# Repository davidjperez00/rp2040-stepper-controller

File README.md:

# rp2040-stepper-controller
This project utilizes the RP2040 microcontroller and A4988 motor drivers on a custom PCB to control NEMA-17 stepper motors. This PCB is equipped with four A4988 providing the ability to drive multiple motors from a single microntroller. Headers pins provide the ability of micro-stepping for each motor. The micro-USB allows for easy flashing from a host machine. The 32MB of external flash memory provide the ability to flash large programs.

## Demo (Click Thumbnail to see Youtube video)

## PCB Snapshots

## Schematic Snapshots

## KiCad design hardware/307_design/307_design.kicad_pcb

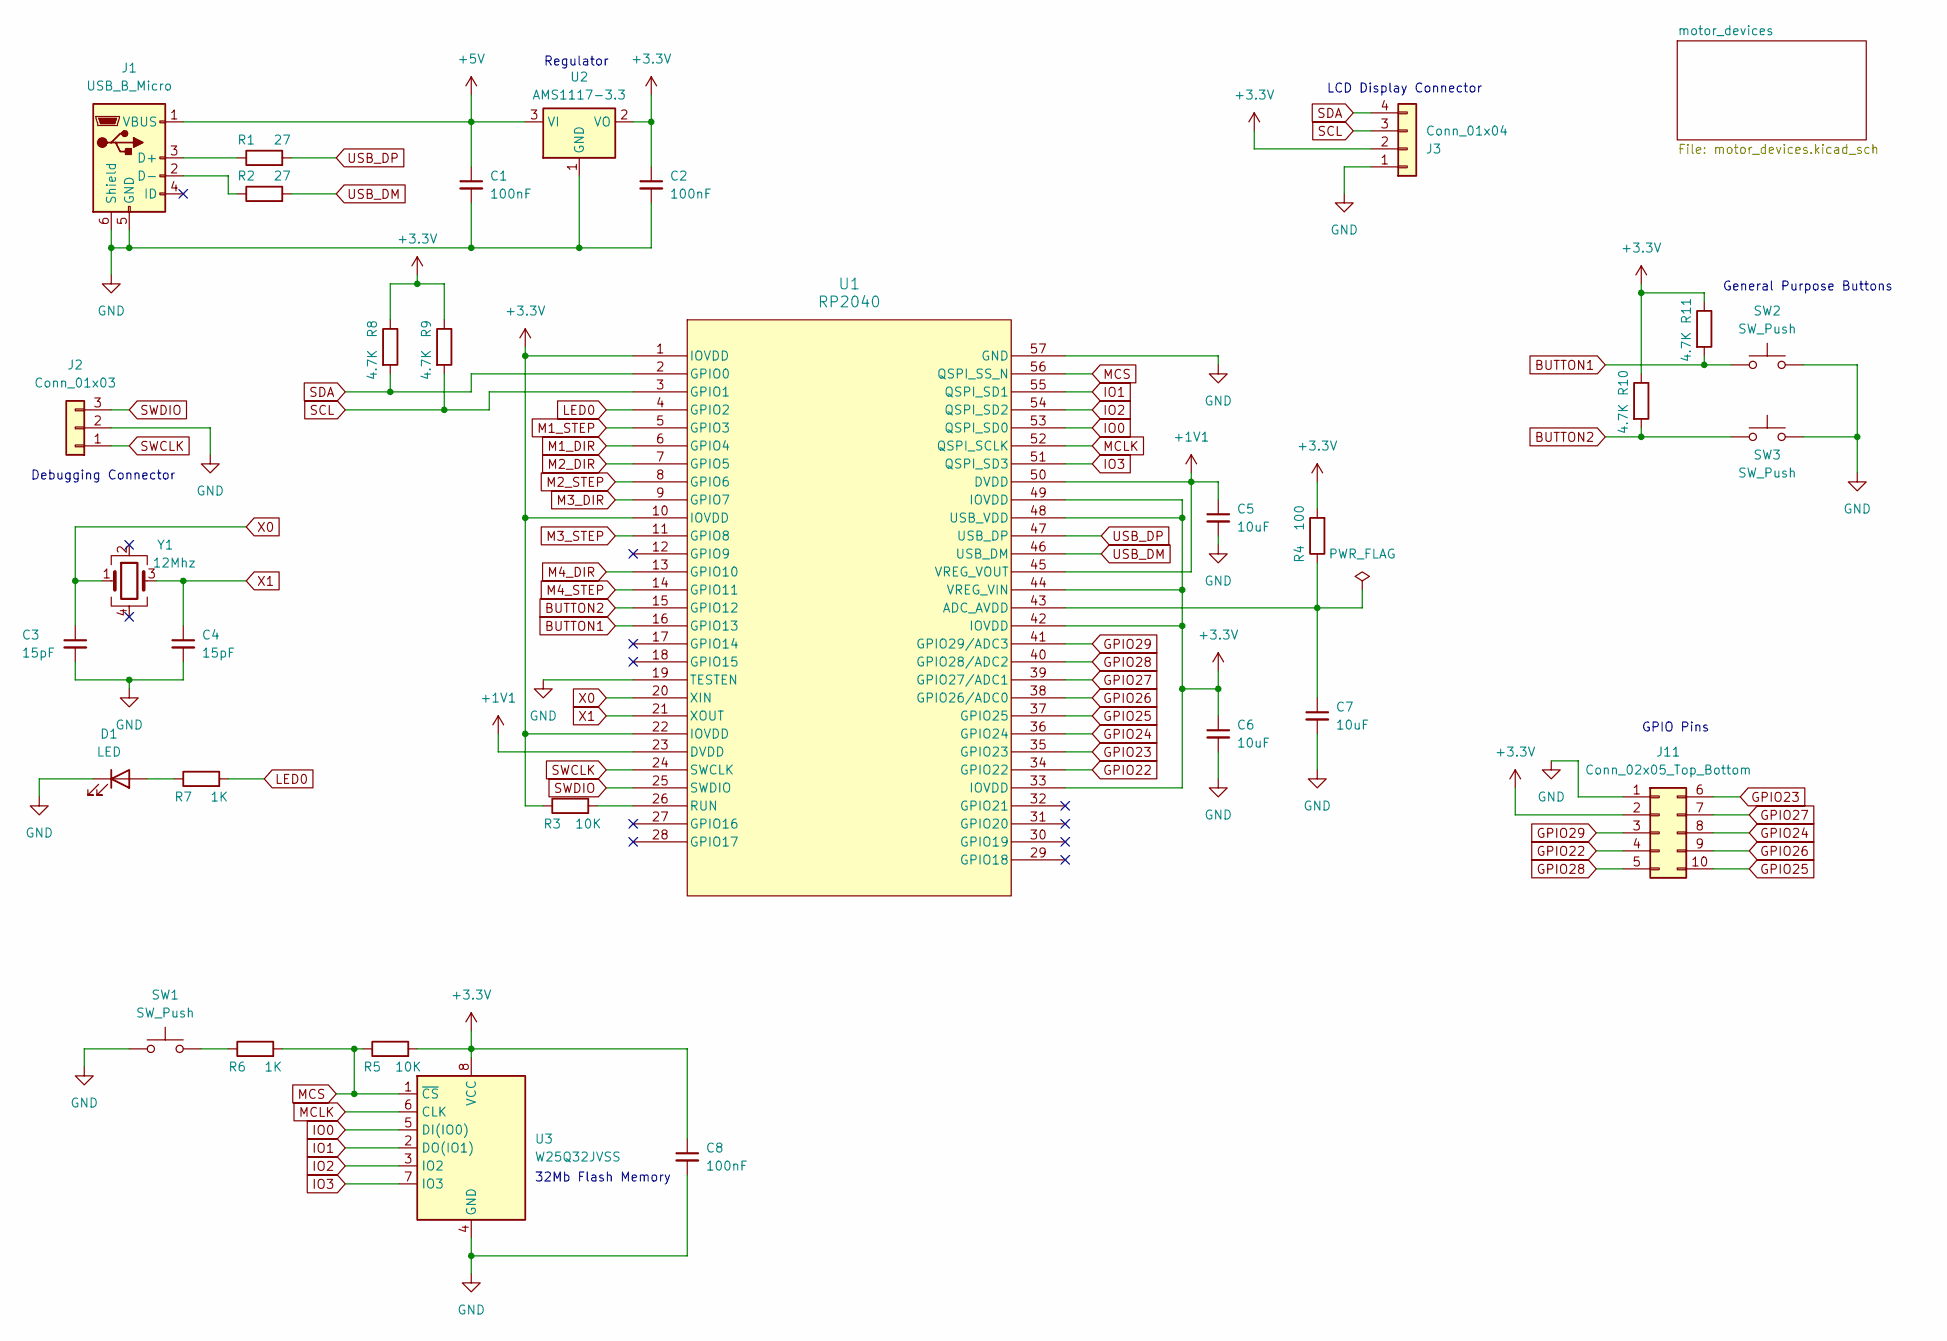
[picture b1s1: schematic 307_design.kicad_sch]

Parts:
C1, C2, C8: 100nF; C_0805_2012Metric
C3, C4: 15pF; C_0805_2012Metric
C5, C6, C7: 10uF; C_0805_2012Metric
D1: LED; LED_0805_2012Metric
J1: USB_B_Micro; USB_Micro-B_Molex_47346-0001
J2: Conn_01x03; PinHeader_1x03_P2.54mm_Vertical
J3: Conn_01x04; PinHeader_1x04_P2.54mm_Vertical
J11: Conn_02x05_Top_Bottom; PinHeader_2x05_P2.54mm_Vertical
R1, R2: 27; R_0805_2012Metric
R3, R5: 10K; R_0805_2012Metric
R4: 100; R_0805_2012Metric
R6, R7: 1K; R_0805_2012Metric
R8, R9, R10, R11: 4.7K; R_0805_2012Metric
SW1, SW2, SW3: SW_Push; SW_SPST_CK_RS282G05A3
U1: RP2040; IC57_RP2040
U2: AMS1117-3.3; SOT-223-3_TabPin2
U3: W25Q32JVSS; SOIC-8_5.23x5.23mm_P1.27mm
Y1: 12Mhz; Crystal_SMD_SeikoEpson_FA238-4Pin_3.2x2.5mm

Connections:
+1V1: C5.1, U1.23 (DVDD), U1.45 (VREG_VOUT), U1.50 (DVDD)
+3.3V: C2.1, C6.1, C8.1, J3.2, J11.2, R3.1, R4.2, R5.2, R8.1, R9.1, R10.1, R11.1, U1.1 (IOVDD), U1.10 (IOVDD), U1.22 (IOVDD), U1.33 (IOVDD), U1.42 (IOVDD), U1.44 (VREG_VIN), U1.48 (USB_VDD), U1.49 (IOVDD), U2.2 (VO), U3.8 (VCC); also elsewhere on the board
+5V: C1.1, J1.1 (VBUS), U2.3 (VI)
BUTTON1: R11.2, SW2.1, U1.16 (GPIO13)
BUTTON2: R10.2, SW3.1, U1.15 (GPIO12)
GPIO22: J11.4, U1.34 (GPIO22)
GPIO23: J11.6, U1.35 (GPIO23)
GPIO24: J11.8, U1.36 (GPIO24)
GPIO25: J11.10, U1.37 (GPIO25)
GPIO26: J11.9, U1.38 (GPIO26/ADC0)
GPIO27: J11.7, U1.39 (GPIO27/ADC1)
GPIO28: J11.5, U1.40 (GPIO28/ADC2)
GPIO29: J11.3, U1.41 (GPIO29/ADC3)
IO0: U1.53 (QSPI_SD0), U3.5 (DI(IO0))
IO1: U1.55 (QSPI_SD1), U3.2 (DO(IO1))
IO2: U1.54 (QSPI_SD2), U3.3 (IO2)
IO3: U1.51 (QSPI_SD3), U3.7 (IO3)
LED0: R7.2, U1.4 (GPIO2)
M1_DIR: U1.6 (GPIO4); also elsewhere on the board
M1_STEP: U1.5 (GPIO3); also elsewhere on the board
M2_DIR: U1.7 (GPIO5); also elsewhere on the board
M2_STEP: U1.8 (GPIO6); also elsewhere on the board
M3_DIR: U1.9 (GPIO7); also elsewhere on the board
M3_STEP: U1.11 (GPIO8); also elsewhere on the board
M4_DIR: U1.13 (GPIO10); also elsewhere on the board
M4_STEP: U1.14 (GPIO11); also elsewhere on the board
MCLK: U1.52 (QSPI_SCLK), U3.6 (CLK)
MCS: R5.1, R6.2, U1.56 (QSPI_SS_N), U3.1 (~CS)
unnamed: D1.2 (A), R7.1
unnamed: J1.3 (D+), R1.1
unnamed: J1.2 (D-), R2.1
unnamed: R6.1, SW1.2
unnamed: C7.1, R4.1, U1.43 (ADC_AVDD)
unnamed: R3.2, U1.26 (RUN)
SCL: J3.3, R9.2, U1.3 (GPIO1)
SDA: J3.4, R8.2, U1.2 (GPIO0)
SWCLK: J2.1, U1.24 (SWCLK)
SWDIO: J2.3, U1.25 (SWDIO)
USB_DM: R2.2, U1.46 (USB_DM)
USB_DP: R1.2, U1.47 (USB_DP)
X0: C3.1, U1.20 (XIN), Y1.1
X1: C4.1, U1.21 (XOUT), Y1.3

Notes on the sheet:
General Purpose Buttons
Debugging Connector
GPIO Pins
LCD Display Connector
Regulator
32Mb Flash Memory

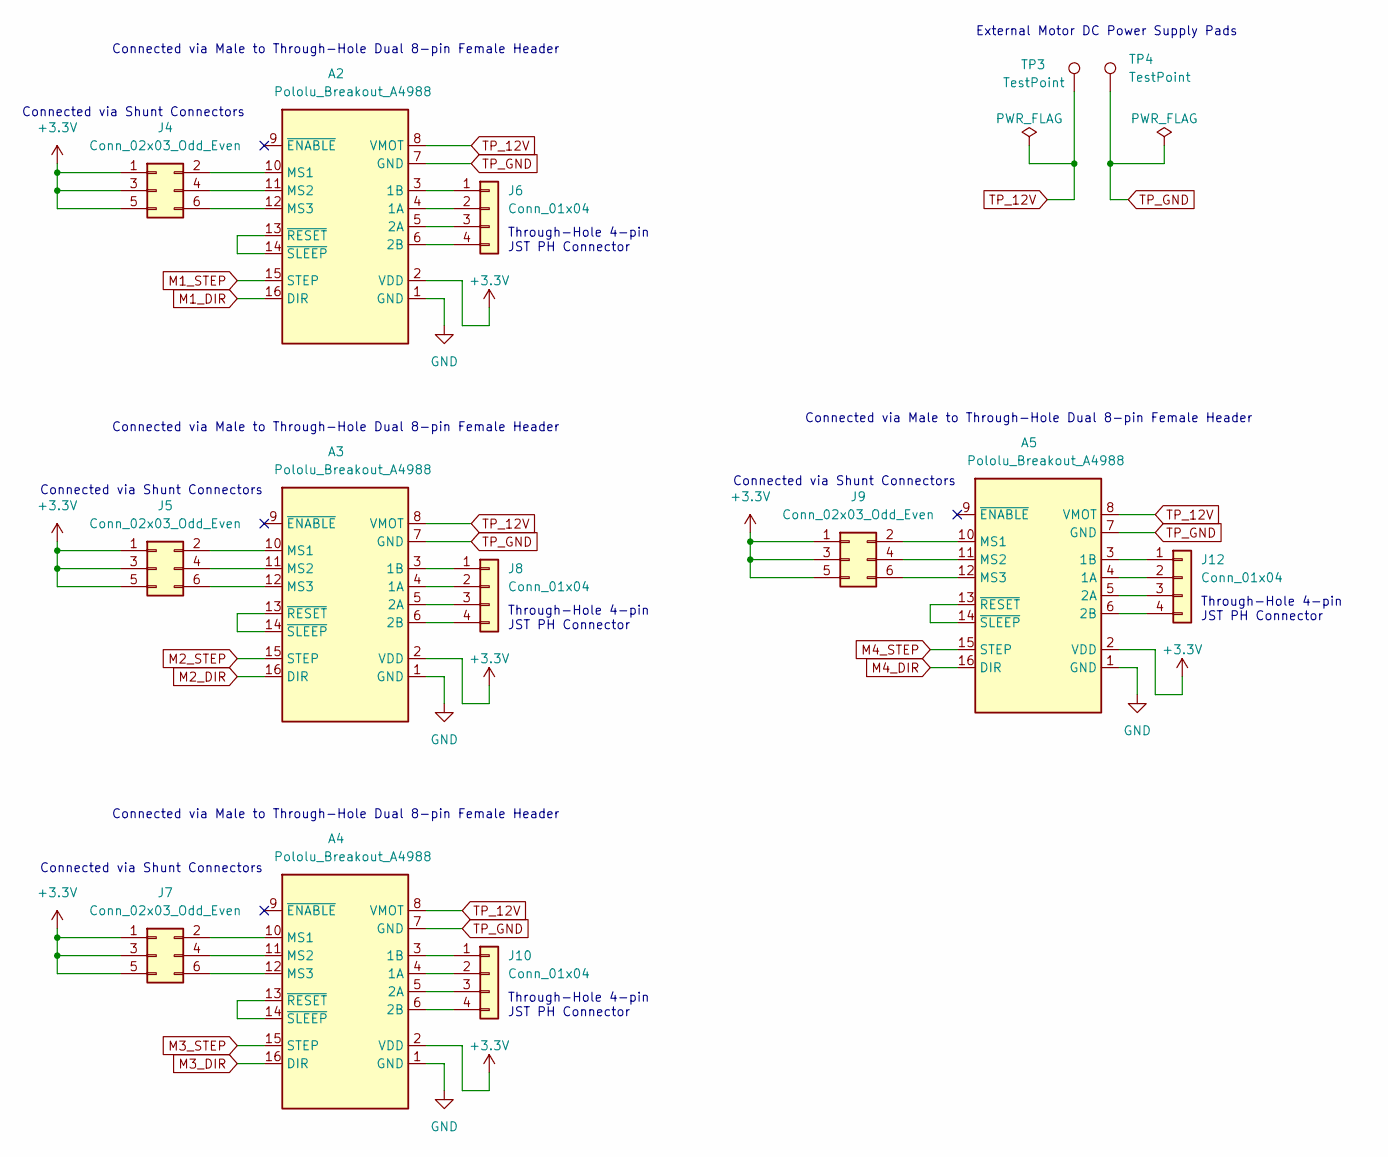
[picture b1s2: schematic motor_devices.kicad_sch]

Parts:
A2, A3, A4, A5: Pololu_Breakout_A4988; Pololu_Breakout-16_15.2x20.3mm
J4, J5, J7, J9: Conn_02x03_Odd_Even; PinHeader_2x03_P2.54mm_Vertical
J6, J8, J10, J12: Conn_01x04; JST_PH_B4B-PH-K_1x04_P2.00mm_Vertical
TP3, TP4: TestPoint; TestPoint_Pad_2.0x2.0mm

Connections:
+3.3V: A2.2 (VDD), A3.2 (VDD), A4.2 (VDD), A5.2 (VDD), J4.1, J4.3, J4.5, J5.1, J5.3, J5.5, J7.1, J7.3, J7.5, J9.1, J9.3, J9.5; also elsewhere on the board
M1_DIR: A2.16 (DIR); also elsewhere on the board
M1_STEP: A2.15 (STEP); also elsewhere on the board
M2_DIR: A3.16 (DIR); also elsewhere on the board
M2_STEP: A3.15 (STEP); also elsewhere on the board
M3_DIR: A4.16 (DIR); also elsewhere on the board
M3_STEP: A4.15 (STEP); also elsewhere on the board
M4_DIR: A5.16 (DIR); also elsewhere on the board
M4_STEP: A5.15 (STEP); also elsewhere on the board
unnamed: A2.4 (1A), J6.2
unnamed: A2.3 (1B), J6.1
unnamed: A2.5 (2A), J6.3
unnamed: A2.6 (2B), J6.4
unnamed: A2.10 (MS1), J4.2
unnamed: A2.11 (MS2), J4.4
unnamed: A2.12 (MS3), J4.6
unnamed: A2.13 (~RESET), A2.14 (~SLEEP)
unnamed: A3.4 (1A), J8.2
unnamed: A3.3 (1B), J8.1
unnamed: A3.5 (2A), J8.3
unnamed: A3.6 (2B), J8.4
unnamed: A3.10 (MS1), J5.2
unnamed: A3.11 (MS2), J5.4
unnamed: A3.12 (MS3), J5.6
unnamed: A3.13 (~RESET), A3.14 (~SLEEP)
unnamed: A4.4 (1A), J10.2
unnamed: A4.3 (1B), J10.1
unnamed: A4.5 (2A), J10.3
unnamed: A4.6 (2B), J10.4
unnamed: A4.10 (MS1), J7.2
unnamed: A4.11 (MS2), J7.4
unnamed: A4.12 (MS3), J7.6
unnamed: A4.13 (~RESET), A4.14 (~SLEEP)
unnamed: A5.4 (1A), J12.2
unnamed: A5.3 (1B), J12.1
unnamed: A5.5 (2A), J12.3
unnamed: A5.6 (2B), J12.4
unnamed: A5.10 (MS1), J9.2
unnamed: A5.11 (MS2), J9.4
unnamed: A5.12 (MS3), J9.6
unnamed: A5.13 (~RESET), A5.14 (~SLEEP)
TP_12V: A2.8 (VMOT), A3.8 (VMOT), A4.8 (VMOT), A5.8 (VMOT), TP3.1

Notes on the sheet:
Connected via Shunt Connectors
External Motor DC Power Supply Pads
Connected via Male to Through-Hole Dual 8-pin Female Header
Through-Hole 4-pin JST PH Connector

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
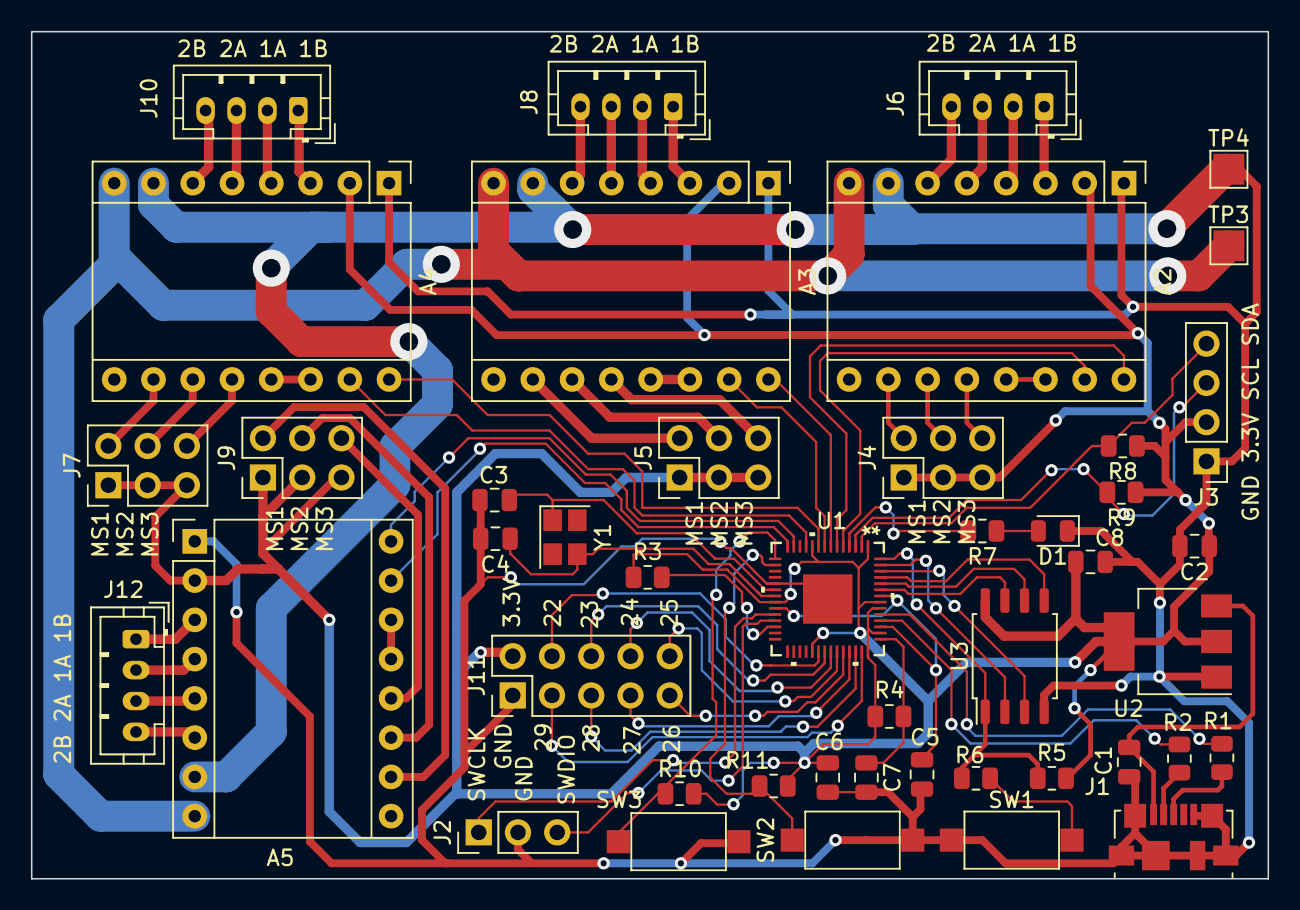
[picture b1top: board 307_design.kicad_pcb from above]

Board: 2 copper layers, 80.0 x 54.8 mm, 45 parts (0 on the bottom side), 76 nets.

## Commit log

2026-01-20 Upload previous hardware implementation
2026-01-22 update traces and add sample program
2026-01-22 Update Readme and add media
2026-01-22 Add Demo thumbnail link to readme
2026-01-27 update readme to use youtube video redirect
2026-01-27 fix typo
